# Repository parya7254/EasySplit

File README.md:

# EasySplit
A hot-swappable split keyboard with a traditional Layout! It will feature MX Switches, a nice!nano (clone) as the main MCU for both sides, and a battery so that it can be used on the go!

# Why Did I Make This??
In school, I type A LOT. And typing on a school chromebook, is well, okay I guess, and I want to have a better typing experience when I type things, and well, I like making my own things and finding my own solutions. So I made this split keyboard. It's wireless, battery-powered, and best of all, **made by ME**. This keyboard will help me type my essays faster, work more efficiently, and also turn in my assignments **ON TIME**. *Ahhh*, yes, that's the feeling of making your own solutions and being proud of it.

# How Was it Made??

The PCB was designed using KiCAD and the case for it was designed in Fusion360. The pictures of the schematic and the PCB are below: 

This is the schematic which was designed in KiCad:

And this is the actual PCB which was also designed in KiCad:

# BOM
These will be the parts that I will use to build and assemble my split keyboard along with the links to get them:

| Name | Purpose | Quantity | Total Cost (USD) | Link | Distributor |
|---|---|---|---|---|---|
| PCB Mount Stabilizers Set | These will prevent wobble when pressing longer keys from the sides! | 1 | 9.99 | https://www.amazon.com/GLORIOUS-Stabilizer-Mechanical-Keyboards-Compatible/dp/B09MZKFLXP/ref=sr_1_11?crid=3RFHAMHTNJHMG&dib=eyJ2IjoiMSJ9.9YfniIYaI-o34quoUu90m7zDr_4-foZ02jjPyDsEARzManorqQYa6ZkiAFErbBYz9TJuFXxpvDujok1W_1GRjgDa590DVzDtTGkG6Xh_kpqE4J4WVSiltDxGBJGeT53EcB3SBohweSioHIYonhLunzFAnVlRzmlw392s7P5Y-ygEsz6do-rmtYWQWlLm-_e1SrFS_aQOEGLgY0bUju37htZfIy6dxoZGQ2pbllG9UMk.Yb2CN95_rwPP4mfPHbmCvu_JmEHeBNfJUVtKBVDAguc&dib_tag=se&keywords=pcb+mount+stabilizers&qid=1776718122&sprefix=pcb+mount+stab%2Caps%2C190&sr=8-11 | Amazon |
| MX Hotswap Sockets (110pcs) | These will be the hotswap sockets for my split keyboard! They will allow for the switches to be removable and replaceable. | 1 | 7.99 | https://www.aliexpress.us/item/3256807045726008.html?spm=a2g0o.productlist.0.0.657f320fXHTJl2&mp=1&pdp_npi=6%40dis%21USD%21USD+15.68%21USD+7.99%21%21USD+7.91%21%21%21%402103212317767176015606506e49b7%2112000039893759777%21ct%21US%21861143113%21%211%210%21&gatewayAdapt=glo2usa | AliExpress |
| 2.0mm JST Connector 2 Pin (5 Pairs) | This will be used to connect the battery to the nice!nano and using this, the battery can also be quickly removed without needing to be desoldered in case of problems or to power off the keyboard. | 1 | 1.76 | https://www.aliexpress.us/item/3256802377876396.html?spm=a2g0o.productlist.main.2.528bk41Bk41BIr&algo_pvid=a5cc2e91-e8b2-44ad-ad58-03e8853783e8&algo_exp_id=a5cc2e91-e8b2-44ad-ad58-03e8853783e8-1&pdp_ext_f=%7B%22order%22%3A%223327%22%2C%22eval%22%3A%221%22%2C%22fromPage%22%3A%22search%22%7D&pdp_npi=6%40dis%21USD%211.81%211.76%21%21%211.81%211.76%21%402101e07217766497385135832ef455%2112000021168869428%21sea%21US%21861143113%21X%211%210%21n_tag%3A-29919%3Bd%3A19af3db4%3Bm03_new_user%3A-29895&curPageLogUid=LA39YhNAYM0j&utparam-url=scene%3Asearch%7Cquery_from%3A%7Cx_object_id%3A1005002564191148%7C_p_origin_prod%3A | AliExpress |
| nice!nano Clone | This will be the main MCU for both sides of my keyboard! It will basically read the key presses and send the respective key commands to the connected device. And it also has Bluetooth and a charging IC which means that the two halves of my split keyboard would be wirelessly connected and I can also directly charge my battery from it. | 2 | 5.52 | https://www.aliexpress.us/item/3256807196955871.html?spm=a2g0o.productlist.main.2.3ce24221tMfSLb&algo_pvid=779ced16-8c06-4ba7-8c56-df3f4f68349a&algo_exp_id=779ced16-8c06-4ba7-8c56-df3f4f68349a-1&pdp_ext_f=%7B%22order%22%3A%221388%22%2C%22eval%22%3A%221%22%2C%22fromPage%22%3A%22search%22%7D&pdp_npi=6%40dis%21USD%212.76%212.76%21%21%212.76%212.76%21%402101e2b617766476966281993eb7ff%2112000047100969961%21sea%21US%21861143113%21X%211%210%21n_tag%3A-29919%3Bd%3A19af3db4%3Bm03_new_user%3A-29895&curPageLogUid=SquxnhThzcZj&utparam-url=scene%3Asearch%7Cquery_from%3A%7Cx_object_id%3A1005007383270623%7C_p_origin_prod%3A | AliExpress |
| 1N4148W SMD Small Signal Fast Switching Diodes (100pcs) | These will be the diodes that will be used in my switch matrix that will also help the microcontroller to read the pressed switches properly! | 1 | 1.38 | https://www.aliexpress.us/item/3256805388348871.html?spm=a2g0o.productlist.main.5.3b99CEnvCEnvvu&algo_pvid=07492d90-a3b7-4c77-a77a-7ac091250105&algo_exp_id=07492d90-a3b7-4c77-a77a-7ac091250105-4&pdp_ext_f=%7B%22order%22%3A%22188%22%2C%22eval%22%3A%221%22%2C%22fromPage%22%3A%22search%22%7D&pdp_npi=6%40dis%21USD%211.38%211.38%21%21%219.40%219.40%21%402103212317766487710596971e49be%2112000033607802195%21sea%21US%21861143113%21X%211%210%21n_tag%3A-29919%3Bd%3A19af3db4%3Bm03_new_user%3A-29895&curPageLogUid=HwWnlNgIq0oD&utparam-url=scene%3Asearch%7Cquery_from%3A%7Cx_object_id%3A1005005574663623%7C_p_origin_prod%3A | AliExpress |
| ELUTENG Ice Blue Mechanical Keyboard Switches (100pcs) | These will be the switches that will be used in my keyboard! | 1 | 15.99 | https://www.amazon.com/gp/product/B0DHCLLH33/ref=ewc_pr_img_1?smid=A3GES9IA7UE877&th=1 | Amazon |
| 3.7V Battery (2pcs) | This will be the battery that will power both halves of my keyboard! | 1 | 8.35 | https://www.aliexpress.us/item/3256811793052939.html?spm=a2g0o.productlist.main.2.23c36977YjUcwi&algo_pvid=7580c894-dc23-495c-9eec-c1519ccc4fcb&algo_exp_id=7580c894-dc23-495c-9eec-c1519ccc4fcb-1&pdp_ext_f=%7B%22order%22%3A%2214%22%2C%22eval%22%3A%221%22%2C%22fromPage%22%3A%22search%22%7D&pdp_npi=6%40dis%21USD%2110.10%216.77%21%21%2168.60%2145.96%21%4021033d9d17766495366072792e2a75%2112000057189289229%21sea%21US%21861143113%21X%211%210%21n_tag%3A-29919%3Bd%3A19af3db4%3Bm03_new_user%3A-29895&curPageLogUid=TjlHmkcBk2xm&utparam-url=scene%3Asearch%7Cquery_from%3A%7Cx_object_id%3A1005011979367691%7C_p_origin_prod%3A | AliExpress |
| Keycap Set | These will be the keycaps that I will use for my keyboard! | 1 | 14.39 | https://www.amazon.com/gp/product/B0BK3HK7SR/ref=ox_sc_act_image_1?smid=A157804XWFVRE0&th=1 | Amazon |
| PCB (Left and Right) MOQ: 5 | This will be my split keyboard's circuit board! | 5 | 34.00 | https://jlcpcb.com/ | JLCPCB |

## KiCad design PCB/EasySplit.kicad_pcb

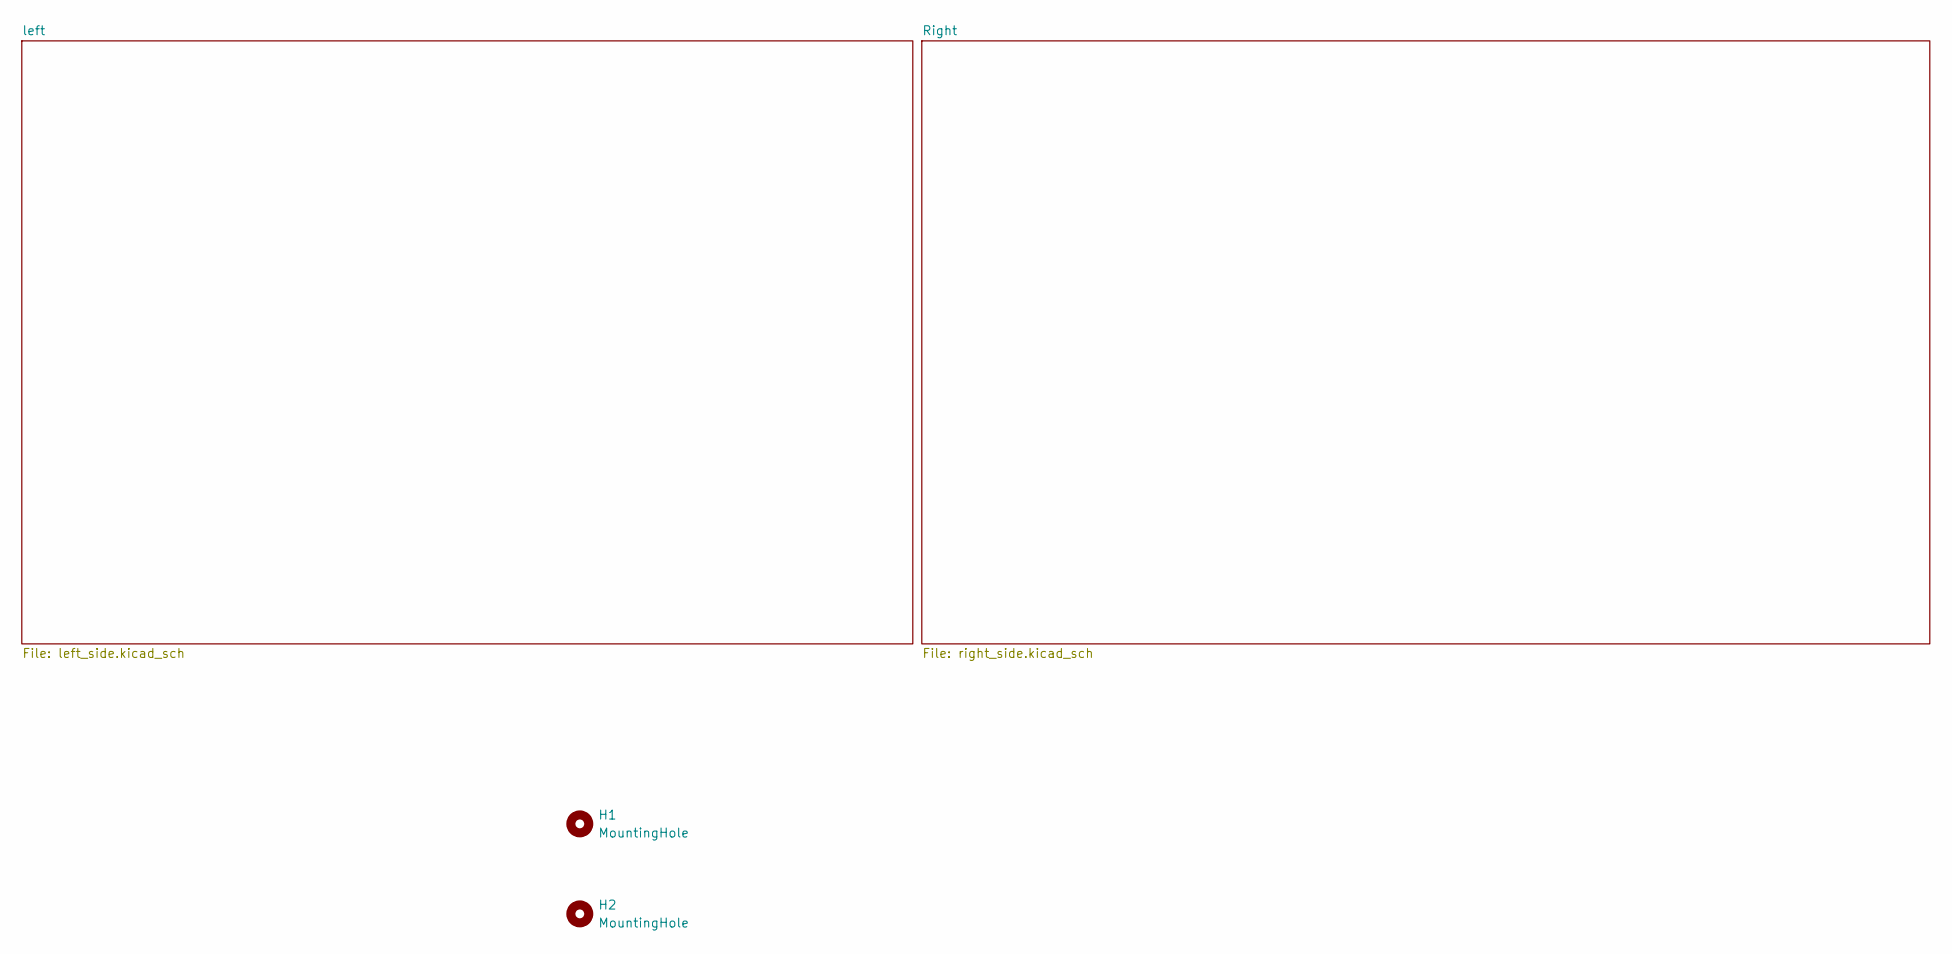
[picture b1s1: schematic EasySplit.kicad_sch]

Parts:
H1, H2: MountingHole; mouse-bite-5mm-slot

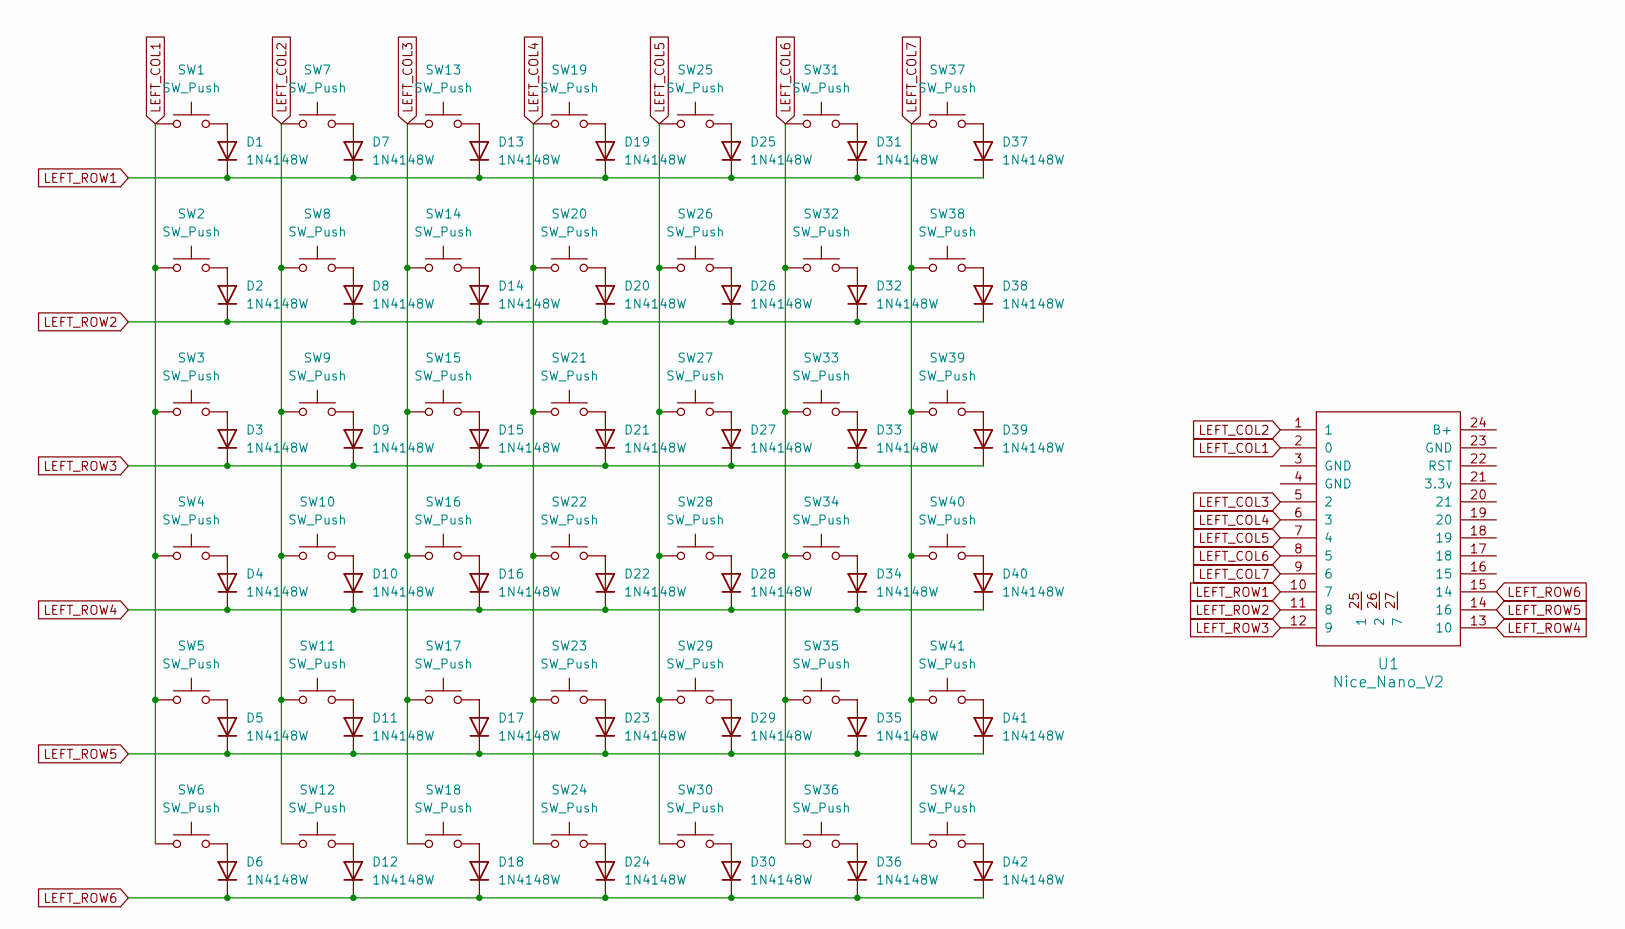
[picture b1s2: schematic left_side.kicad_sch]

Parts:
D1, D2, D3, D4, D5, D6, D7, D8, D9, D10, D11, D12, D13, D14, D15, D16, D17, D18, D19, D20, D21, D22, D23, D24, D25, D26, D27, D28, D29, D30, D31, D32, D33, D34, D35, D36, D37, D38, D39, D40, D41, D42: 1N4148W; D_SOD-123
SW1, SW2, SW7, SW8, SW9, SW10, SW11, SW13, SW14, SW15, SW16, SW17, SW19, SW20, SW21, SW22, SW23, SW25, SW26, SW27, SW28, SW29, SW31, SW32, SW33, SW34, SW35, SW36, SW37, SW38, SW39, SW40, SW41, SW42: SW_Push; Hotswap_MX_1.00u
SW3: SW_Push; Hotswap_MX_1.50u
SW4: SW_Push; Hotswap_MX_1.75u
SW5, SW30: SW_Push; Hotswap_MX_2.25u
SW6, SW12, SW18, SW24: SW_Push; Hotswap_MX_1.25u
U1: Nice_Nano_V2

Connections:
LEFT_COL1: SW1.1, SW2.1, SW3.1, SW4.1, SW5.1, SW6.1, U1.2 (0)
LEFT_COL2: SW7.1, SW8.1, SW9.1, SW10.1, SW11.1, SW12.1, U1.1
LEFT_COL3: SW13.1, SW14.1, SW15.1, SW16.1, SW17.1, SW18.1, U1.5 (2)
LEFT_COL4: SW19.1, SW20.1, SW21.1, SW22.1, SW23.1, SW24.1, U1.6 (3)
LEFT_COL5: SW25.1, SW26.1, SW27.1, SW28.1, SW29.1, SW30.1, U1.7 (4)
LEFT_COL6: SW31.1, SW32.1, SW33.1, SW34.1, SW35.1, SW36.1, U1.8 (5)
LEFT_COL7: SW37.1, SW38.1, SW39.1, SW40.1, SW41.1, SW42.1, U1.9 (6)
LEFT_ROW1: D1.1 (K), D7.1 (K), D13.1 (K), D19.1 (K), D25.1 (K), D31.1 (K), D37.1 (K), U1.10 (7)
LEFT_ROW2: D2.1 (K), D8.1 (K), D14.1 (K), D20.1 (K), D26.1 (K), D32.1 (K), D38.1 (K), U1.11 (8)
LEFT_ROW3: D3.1 (K), D9.1 (K), D15.1 (K), D21.1 (K), D27.1 (K), D33.1 (K), D39.1 (K), U1.12 (9)
LEFT_ROW4: D4.1 (K), D10.1 (K), D16.1 (K), D22.1 (K), D28.1 (K), D34.1 (K), D40.1 (K), U1.13 (10)
LEFT_ROW5: D5.1 (K), D11.1 (K), D17.1 (K), D23.1 (K), D29.1 (K), D35.1 (K), D41.1 (K), U1.14 (16)
LEFT_ROW6: D6.1 (K), D12.1 (K), D18.1 (K), D24.1 (K), D30.1 (K), D36.1 (K), D42.1 (K), U1.15 (14)
unnamed: D1.2 (A), SW1.2
unnamed: D2.2 (A), SW2.2
unnamed: D3.2 (A), SW3.2
unnamed: D4.2 (A), SW4.2
unnamed: D5.2 (A), SW5.2
unnamed: D6.2 (A), SW6.2
unnamed: D7.2 (A), SW7.2
unnamed: D8.2 (A), SW8.2
unnamed: D9.2 (A), SW9.2
unnamed: D10.2 (A), SW10.2
unnamed: D11.2 (A), SW11.2
unnamed: D12.2 (A), SW12.2
unnamed: D13.2 (A), SW13.2
unnamed: D14.2 (A), SW14.2
unnamed: D15.2 (A), SW15.2
unnamed: D16.2 (A), SW16.2
unnamed: D17.2 (A), SW17.2
unnamed: D18.2 (A), SW18.2
unnamed: D19.2 (A), SW19.2
unnamed: D20.2 (A), SW20.2
unnamed: D21.2 (A), SW21.2
unnamed: D22.2 (A), SW22.2
unnamed: D23.2 (A), SW23.2
unnamed: D24.2 (A), SW24.2
unnamed: D25.2 (A), SW25.2
unnamed: D26.2 (A), SW26.2
unnamed: D27.2 (A), SW27.2
unnamed: D28.2 (A), SW28.2
unnamed: D29.2 (A), SW29.2
unnamed: D30.2 (A), SW30.2
unnamed: D31.2 (A), SW31.2
unnamed: D32.2 (A), SW32.2
unnamed: D33.2 (A), SW33.2
unnamed: D34.2 (A), SW34.2
unnamed: D35.2 (A), SW35.2
unnamed: D36.2 (A), SW36.2
unnamed: D37.2 (A), SW37.2
unnamed: D38.2 (A), SW38.2
unnamed: D39.2 (A), SW39.2
unnamed: D40.2 (A), SW40.2
unnamed: D41.2 (A), SW41.2
unnamed: D42.2 (A), SW42.2

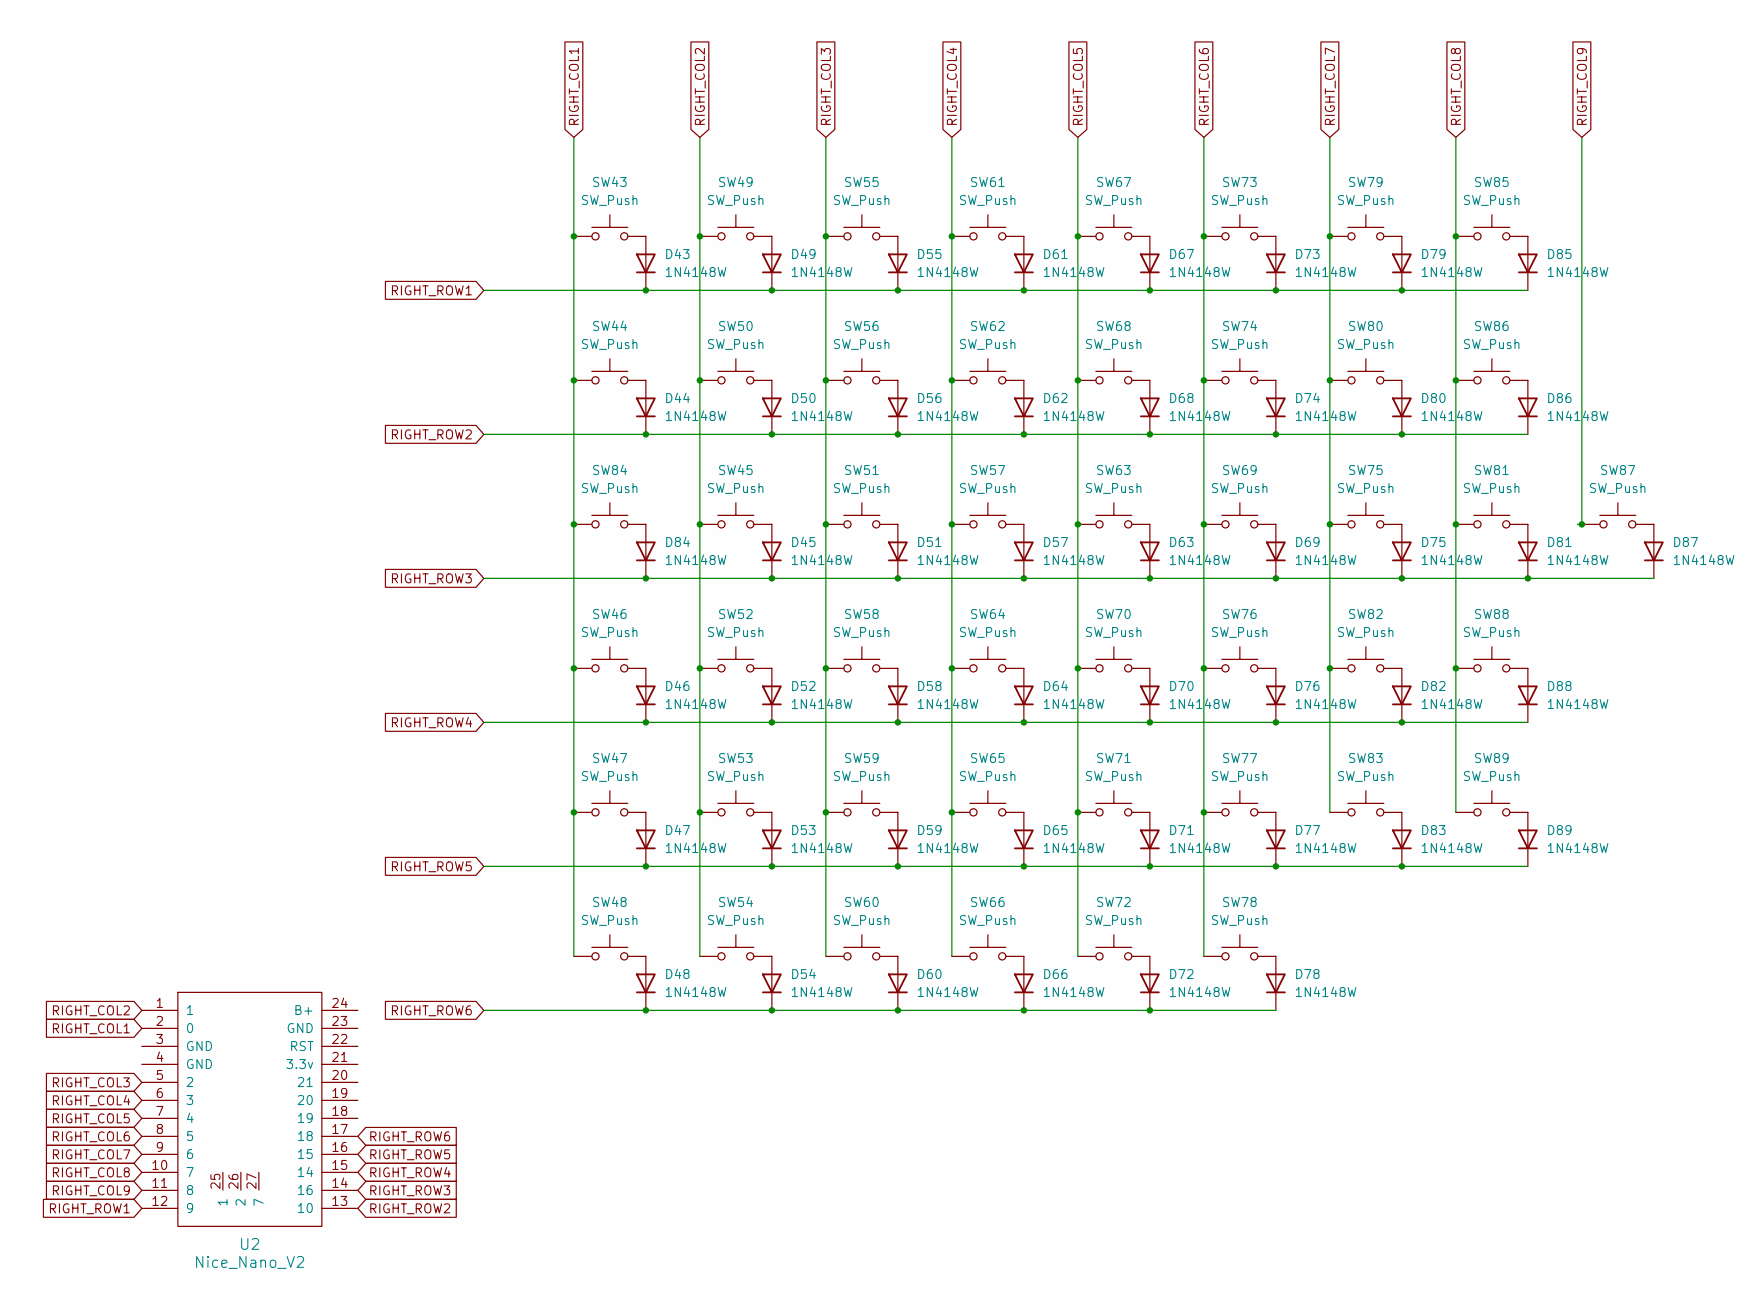
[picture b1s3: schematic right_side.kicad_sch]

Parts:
D43, D44, D45, D46, D47, D48, D49, D50, D51, D52, D53, D54, D55, D56, D57, D58, D59, D60, D61, D62, D63, D64, D65, D66, D67, D68, D69, D70, D71, D72, D73, D74, D75, D76, D77, D78, D79, D80, D81, D82, D83, D84, D85, D86, D87, D88, D89: 1N4148W; D_SOD-123
SW43, SW44, SW45, SW46, SW47, SW49, SW50, SW51, SW52, SW53, SW55, SW56, SW57, SW58, SW59, SW61, SW62, SW63, SW64, SW65, SW66, SW67, SW68, SW69, SW70, SW71, SW72, SW73, SW74, SW75, SW76, SW78, SW79, SW83, SW84, SW85, SW86, SW87, SW88, SW89: SW_Push; Hotswap_MX_1.00u
SW48: SW_Push; Hotswap_MX_2.75u
SW54, SW60, SW81: SW_Push; Hotswap_MX_1.50u
SW77: SW_Push; Hotswap_MX_1.75u
SW80: SW_Push; Hotswap_MX_2.00u
SW82: SW_Push; Hotswap_MX_2.25u
U2: Nice_Nano_V2

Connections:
unnamed: D43.2 (A), SW43.2
unnamed: D44.2 (A), SW44.2
unnamed: D45.2 (A), SW45.2
unnamed: D46.2 (A), SW46.2
unnamed: D47.2 (A), SW47.2
unnamed: D48.2 (A), SW48.2
unnamed: D49.2 (A), SW49.2
unnamed: D50.2 (A), SW50.2
unnamed: D51.2 (A), SW51.2
unnamed: D52.2 (A), SW52.2
unnamed: D53.2 (A), SW53.2
unnamed: D54.2 (A), SW54.2
unnamed: D55.2 (A), SW55.2
unnamed: D56.2 (A), SW56.2
unnamed: D57.2 (A), SW57.2
unnamed: D58.2 (A), SW58.2
unnamed: D59.2 (A), SW59.2
unnamed: D60.2 (A), SW60.2
unnamed: D61.2 (A), SW61.2
unnamed: D62.2 (A), SW62.2
unnamed: D63.2 (A), SW63.2
unnamed: D64.2 (A), SW64.2
unnamed: D65.2 (A), SW65.2
unnamed: D66.2 (A), SW66.2
unnamed: D67.2 (A), SW67.2
unnamed: D68.2 (A), SW68.2
unnamed: D69.2 (A), SW69.2
unnamed: D70.2 (A), SW70.2
unnamed: D71.2 (A), SW71.2
unnamed: D72.2 (A), SW72.2
unnamed: D73.2 (A), SW73.2
unnamed: D74.2 (A), SW74.2
unnamed: D75.2 (A), SW75.2
unnamed: D76.2 (A), SW76.2
unnamed: D77.2 (A), SW77.2
unnamed: D78.2 (A), SW78.2
unnamed: D79.2 (A), SW79.2
unnamed: D80.2 (A), SW80.2
unnamed: D81.2 (A), SW81.2
unnamed: D82.2 (A), SW82.2
unnamed: D83.2 (A), SW83.2
unnamed: D84.2 (A), SW84.2
unnamed: D85.2 (A), SW85.2
unnamed: D86.2 (A), SW86.2
unnamed: D87.2 (A), SW87.2
unnamed: D88.2 (A), SW88.2
unnamed: D89.2 (A), SW89.2
RIGHT_COL1: SW43.1, SW44.1, SW46.1, SW47.1, SW48.1, SW84.1, U2.2 (0)
RIGHT_COL2: SW45.1, SW49.1, SW50.1, SW52.1, SW53.1, SW54.1, U2.1
RIGHT_COL3: SW51.1, SW55.1, SW56.1, SW58.1, SW59.1, SW60.1, U2.5 (2)
RIGHT_COL4: SW57.1, SW61.1, SW62.1, SW64.1, SW65.1, SW66.1, U2.6 (3)
RIGHT_COL5: SW63.1, SW67.1, SW68.1, SW70.1, SW71.1, SW72.1, U2.7 (4)
RIGHT_COL6: SW69.1, SW73.1, SW74.1, SW76.1, SW77.1, SW78.1, U2.8 (5)
RIGHT_COL7: SW75.1, SW79.1, SW80.1, SW82.1, SW83.1, U2.9 (6)
RIGHT_COL8: SW81.1, SW85.1, SW86.1, SW88.1, SW89.1, U2.10 (7)
RIGHT_COL9: SW87.1, U2.11 (8)
RIGHT_ROW1: D43.1 (K), D49.1 (K), D55.1 (K), D61.1 (K), D67.1 (K), D73.1 (K), D79.1 (K), D85.1 (K), U2.12 (9)
RIGHT_ROW2: D44.1 (K), D50.1 (K), D56.1 (K), D62.1 (K), D68.1 (K), D74.1 (K), D80.1 (K), D86.1 (K), U2.13 (10)
RIGHT_ROW3: D45.1 (K), D51.1 (K), D57.1 (K), D63.1 (K), D69.1 (K), D75.1 (K), D81.1 (K), D84.1 (K), D87.1 (K), U2.14 (16)
RIGHT_ROW4: D46.1 (K), D52.1 (K), D58.1 (K), D64.1 (K), D70.1 (K), D76.1 (K), D82.1 (K), D88.1 (K), U2.15 (14)
RIGHT_ROW5: D47.1 (K), D53.1 (K), D59.1 (K), D65.1 (K), D71.1 (K), D77.1 (K), D83.1 (K), D89.1 (K), U2.16 (15)
RIGHT_ROW6: D48.1 (K), D54.1 (K), D60.1 (K), D66.1 (K), D72.1 (K), D78.1 (K), U2.17 (18)

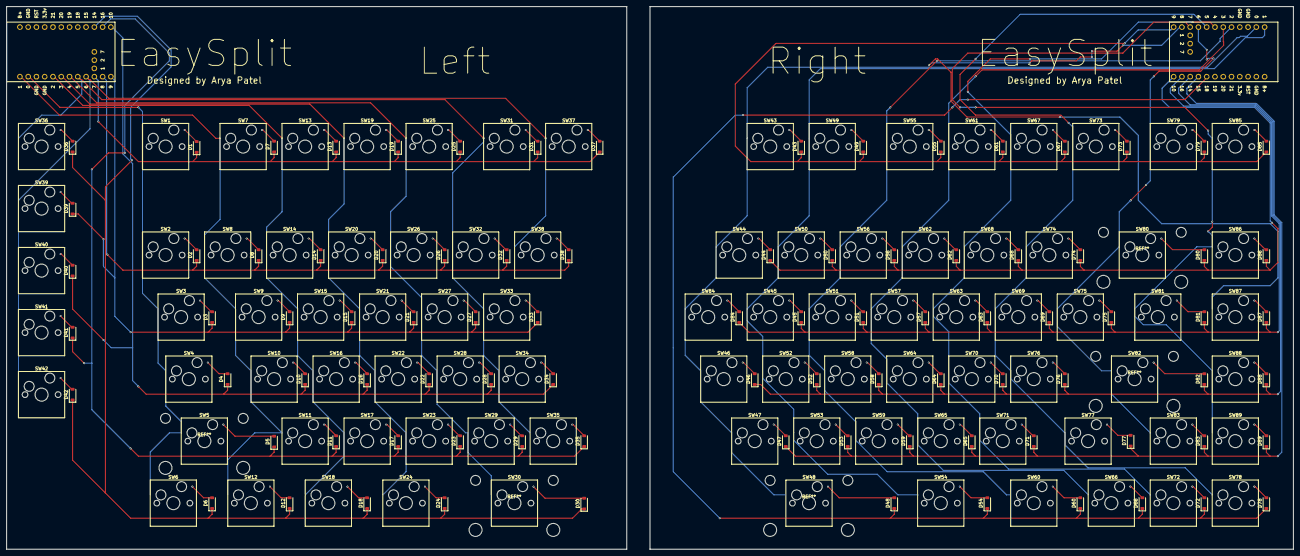
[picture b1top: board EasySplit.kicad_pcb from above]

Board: 2 copper layers, 395.3 x 166.7 mm, 180 parts (0 on the bottom side), 117 nets.

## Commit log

2026-04-10 Update description to specify hot-swappable feature
2026-04-11 Update switch type from low-profile to MX Switches
2026-04-22 Uploaded all files!!
2026-04-22 Revise README for EasySplit keyboard project
    Updated the README to enhance clarity and detail about the EasySplit keyboard project, including the BOM and images.
2026-04-22 Uploaded PCB Files!!
2026-04-23 Update README with new schematic and PCB images
    Added additional images of the schematic and PCB designed in KiCad.
2026-04-24 Organized PCB Files!!
2026-06-29 Enhance README with images and personal motivation
    Added images to README and expanded on the motivation for creating the keyboard.
